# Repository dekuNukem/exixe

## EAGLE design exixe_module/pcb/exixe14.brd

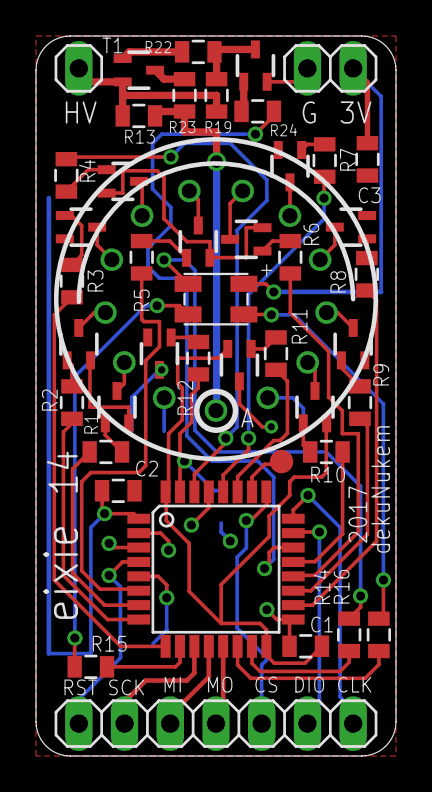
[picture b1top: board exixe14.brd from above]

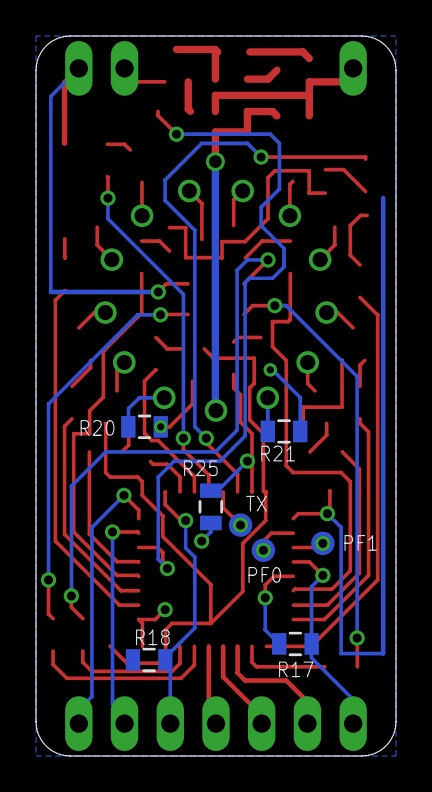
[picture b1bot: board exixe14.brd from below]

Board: 2 copper layers, 20.0 x 40.0 mm, 51 parts (8 on the bottom side), 64 nets.

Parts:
C1: 1uF; 0805
C2, C3: 100nF; 0805
D1: RGB_LED_CA-150141M173100-R&G&B; 3528-COMMON-ANODE
JP1, JP2: 1X07
N1: IN-14
Q1, Q2, Q3, Q4, Q5, Q6, Q7, Q8, Q9, Q10, Q11, Q12, Q13: SOT323
R1, R2, R3, R4, R5, R7, R8, R9, R10, R11, R12, R17, R18, R24: 10K; 0805
R6: 4K7; 0805
R13, R23, R25: 68K; 0805
R14, R16: 330; 0805
R15: 680; 0805
R19, R22: 1M; 0805
R20, R21: 510K; 0805
T1: SOT323
TP1, TP2, TP3, TP4: PTR1TP13R; TP13R
U$2: STM32F042K6; TQFP32-08

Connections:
+3V3: C1.1, C2.1, C3.1, D1.1, JP1.7, R17.2, R18.2, U$2.1, U$2.5, U$2.17
+180V: N1.A, R13.1, R23.1
BAKE: R24.2, U$2.22
GND: C1.2, C2.2, C3.2, JP1.6, Q1.2, Q2.2, Q3.2, Q4.2, Q5.2, Q6.2, Q7.2, Q8.2, Q9.2, Q10.2, Q11.2, Q12.2, Q13.2, R25.1, U$2.16, U$2.32
unnamed: Q1.1, R1.2
unnamed: TP1.TP, U$2.2
unnamed: D1.4, R15.1
unnamed: Q2.1, R2.2
unnamed: Q3.1, R3.2
unnamed: Q4.1, R4.2
unnamed: Q5.1, R5.2
unnamed: Q6.1, R6.2
unnamed: Q7.1, R7.2
unnamed: Q8.1, R8.2
unnamed: Q9.1, R9.2
unnamed: Q10.1, R10.2
unnamed: Q11.1, R11.2
unnamed: Q12.1, R12.2
unnamed: D1.3, R14.1
unnamed: TP2.TP, U$2.3
unnamed: Q12.3, R21.1
unnamed: Q11.3, R20.1
unnamed: JP1.1, R13.2, R19.1, T1.3
unnamed: R22.1, T1.2
unnamed: D1.2, R16.1
unnamed: Q13.3, R19.2, R22.2
unnamed: Q13.1, R24.1
unnamed: R23.2, T1.1
unnamed: TP4.TP, U$2.26
NIXIE_1: N1.1, Q1.3
NIXIE_2: N1.2, Q2.3
NIXIE_3: N1.3, Q3.3
NIXIE_4: N1.4, Q4.3
NIXIE_5: N1.5, Q5.3
NIXIE_6: N1.6, Q6.3
NIXIE_7: N1.7, Q7.3
NIXIE_8: N1.8, Q8.3
NIXIE_9: N1.9, Q9.3
NIXIE_10: N1.0, Q10.3
NIXIE_DOT_LEFT: N1.LHDP, R20.2
NIXIE_DOT_RIGHT: N1.RHDP, R21.2
NRST: JP2.1, R17.1, U$2.4
PWM_BLUE: R16.2, U$2.14
PWM_GREEN: R15.2, U$2.10
PWM_RED: R14.2, U$2.15
SPI_CS: JP2.5, R18.1, U$2.25
SPI_MISO: JP2.3, U$2.12
SPI_MOSI: JP2.4, U$2.13
SPI_SCK: JP2.2, U$2.11
STM_1: R1.1, U$2.7
STM_2: R2.1, U$2.8
STM_3: R3.1, U$2.9
STM_4: R4.1, U$2.30
STM_5: R5.1, U$2.6
STM_6: R6.1, U$2.20
STM_7: R7.1, U$2.28
STM_8: R8.1, U$2.18
STM_9: R9.1, U$2.19
STM_10: R10.1, U$2.21
STM_DOT_LEFT: R11.1, U$2.27
STM_DOT_RIGHT: R12.1, R25.2, U$2.31
SWD_CLK: JP2.7, U$2.24
SWD_DIO: JP2.6, U$2.23
UART_TX: TP3.TP, U$2.29

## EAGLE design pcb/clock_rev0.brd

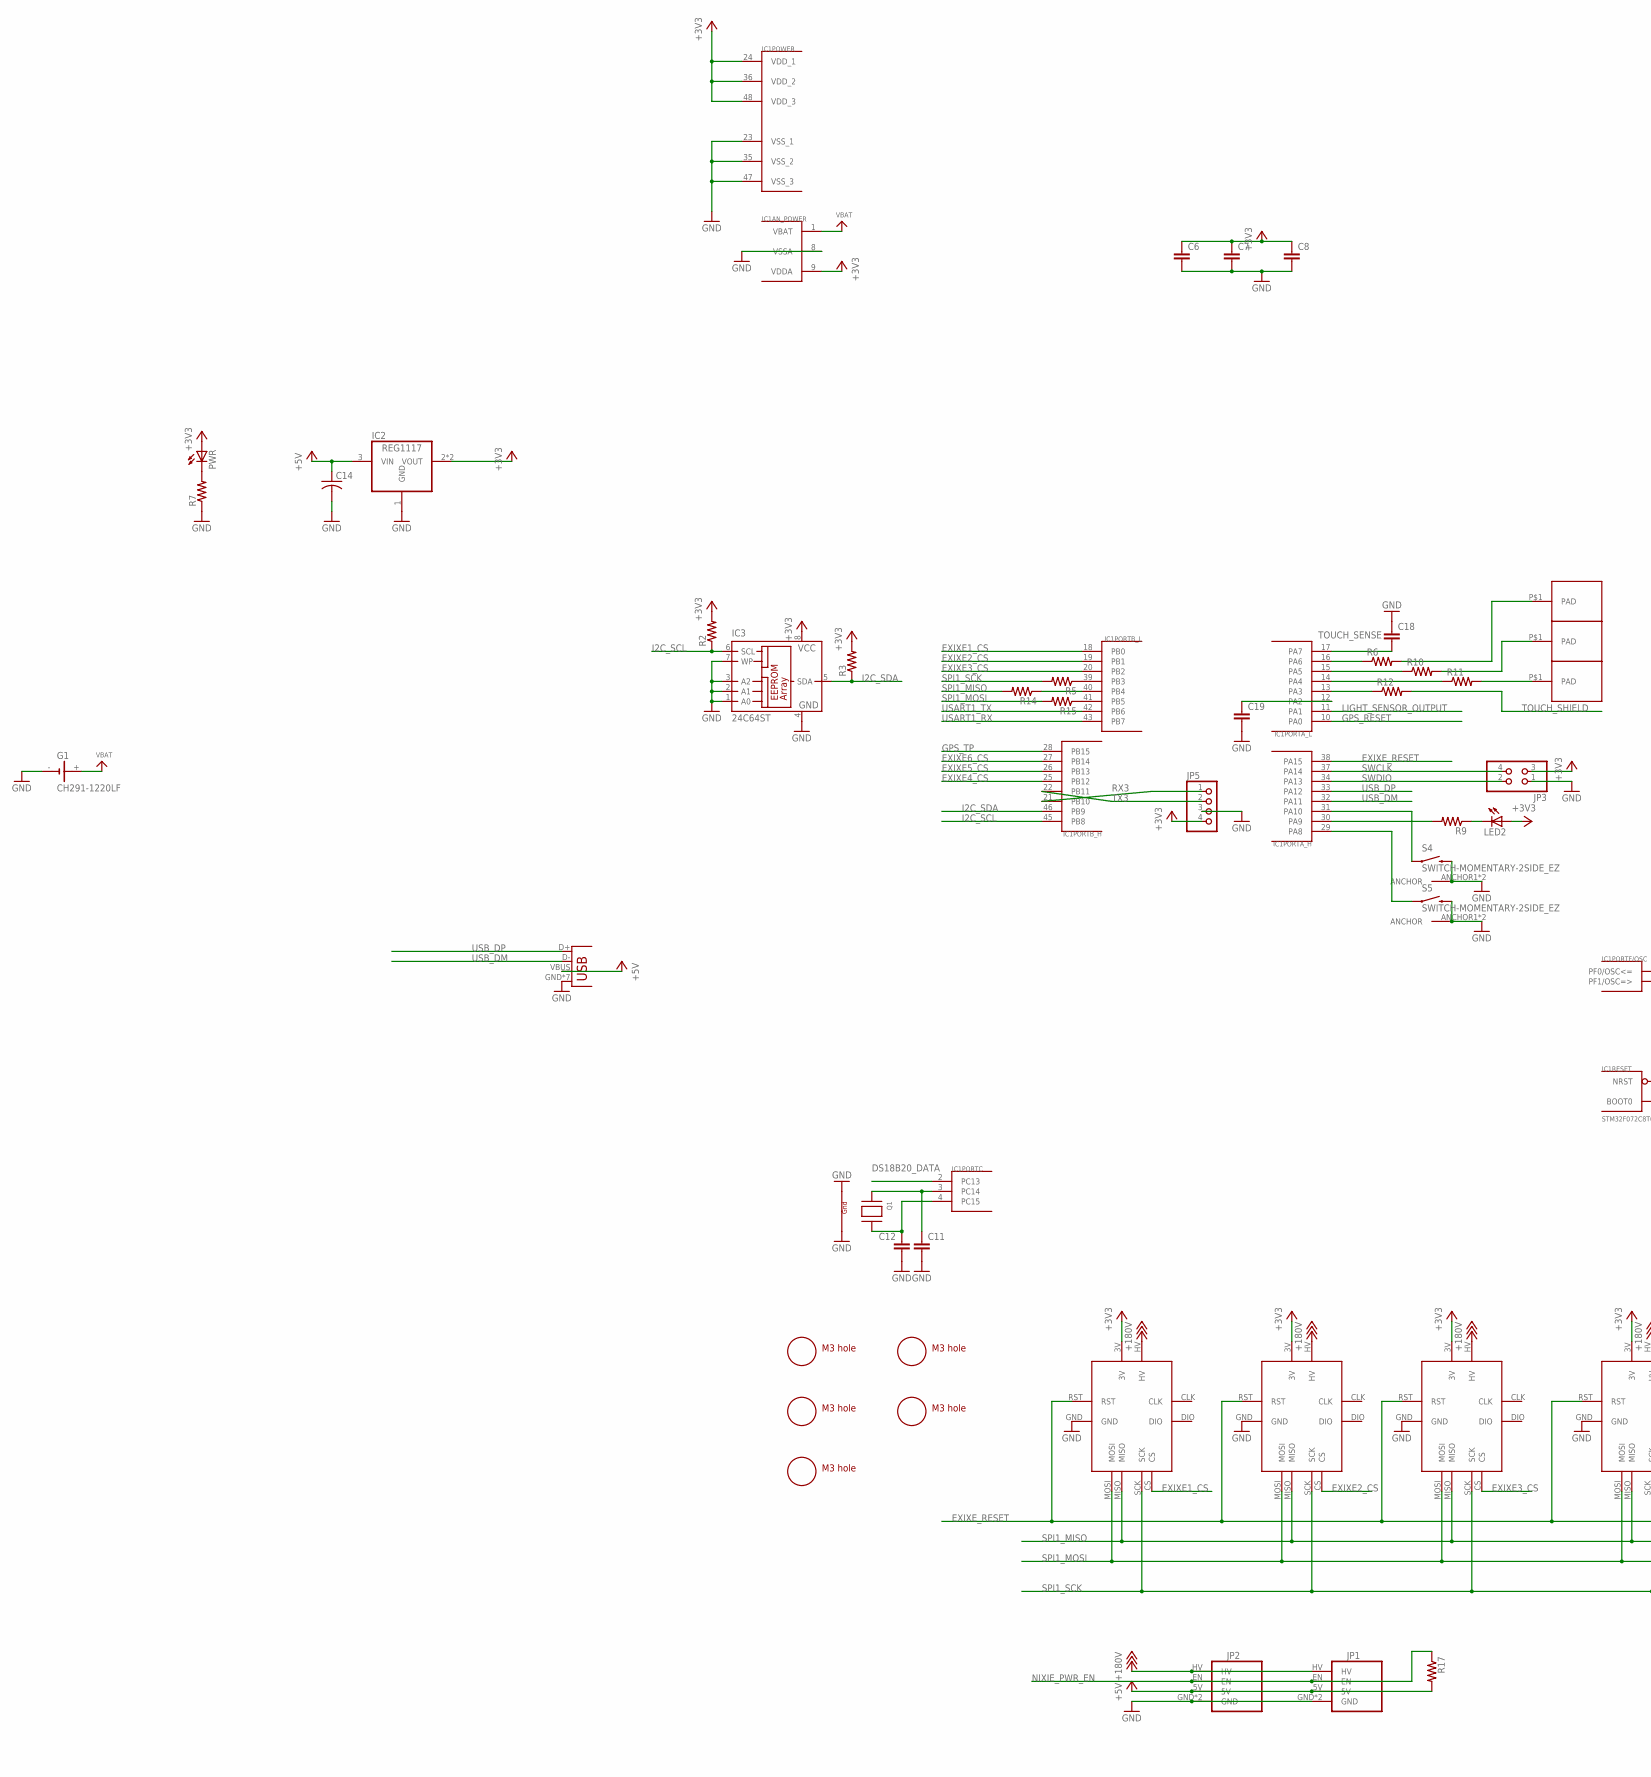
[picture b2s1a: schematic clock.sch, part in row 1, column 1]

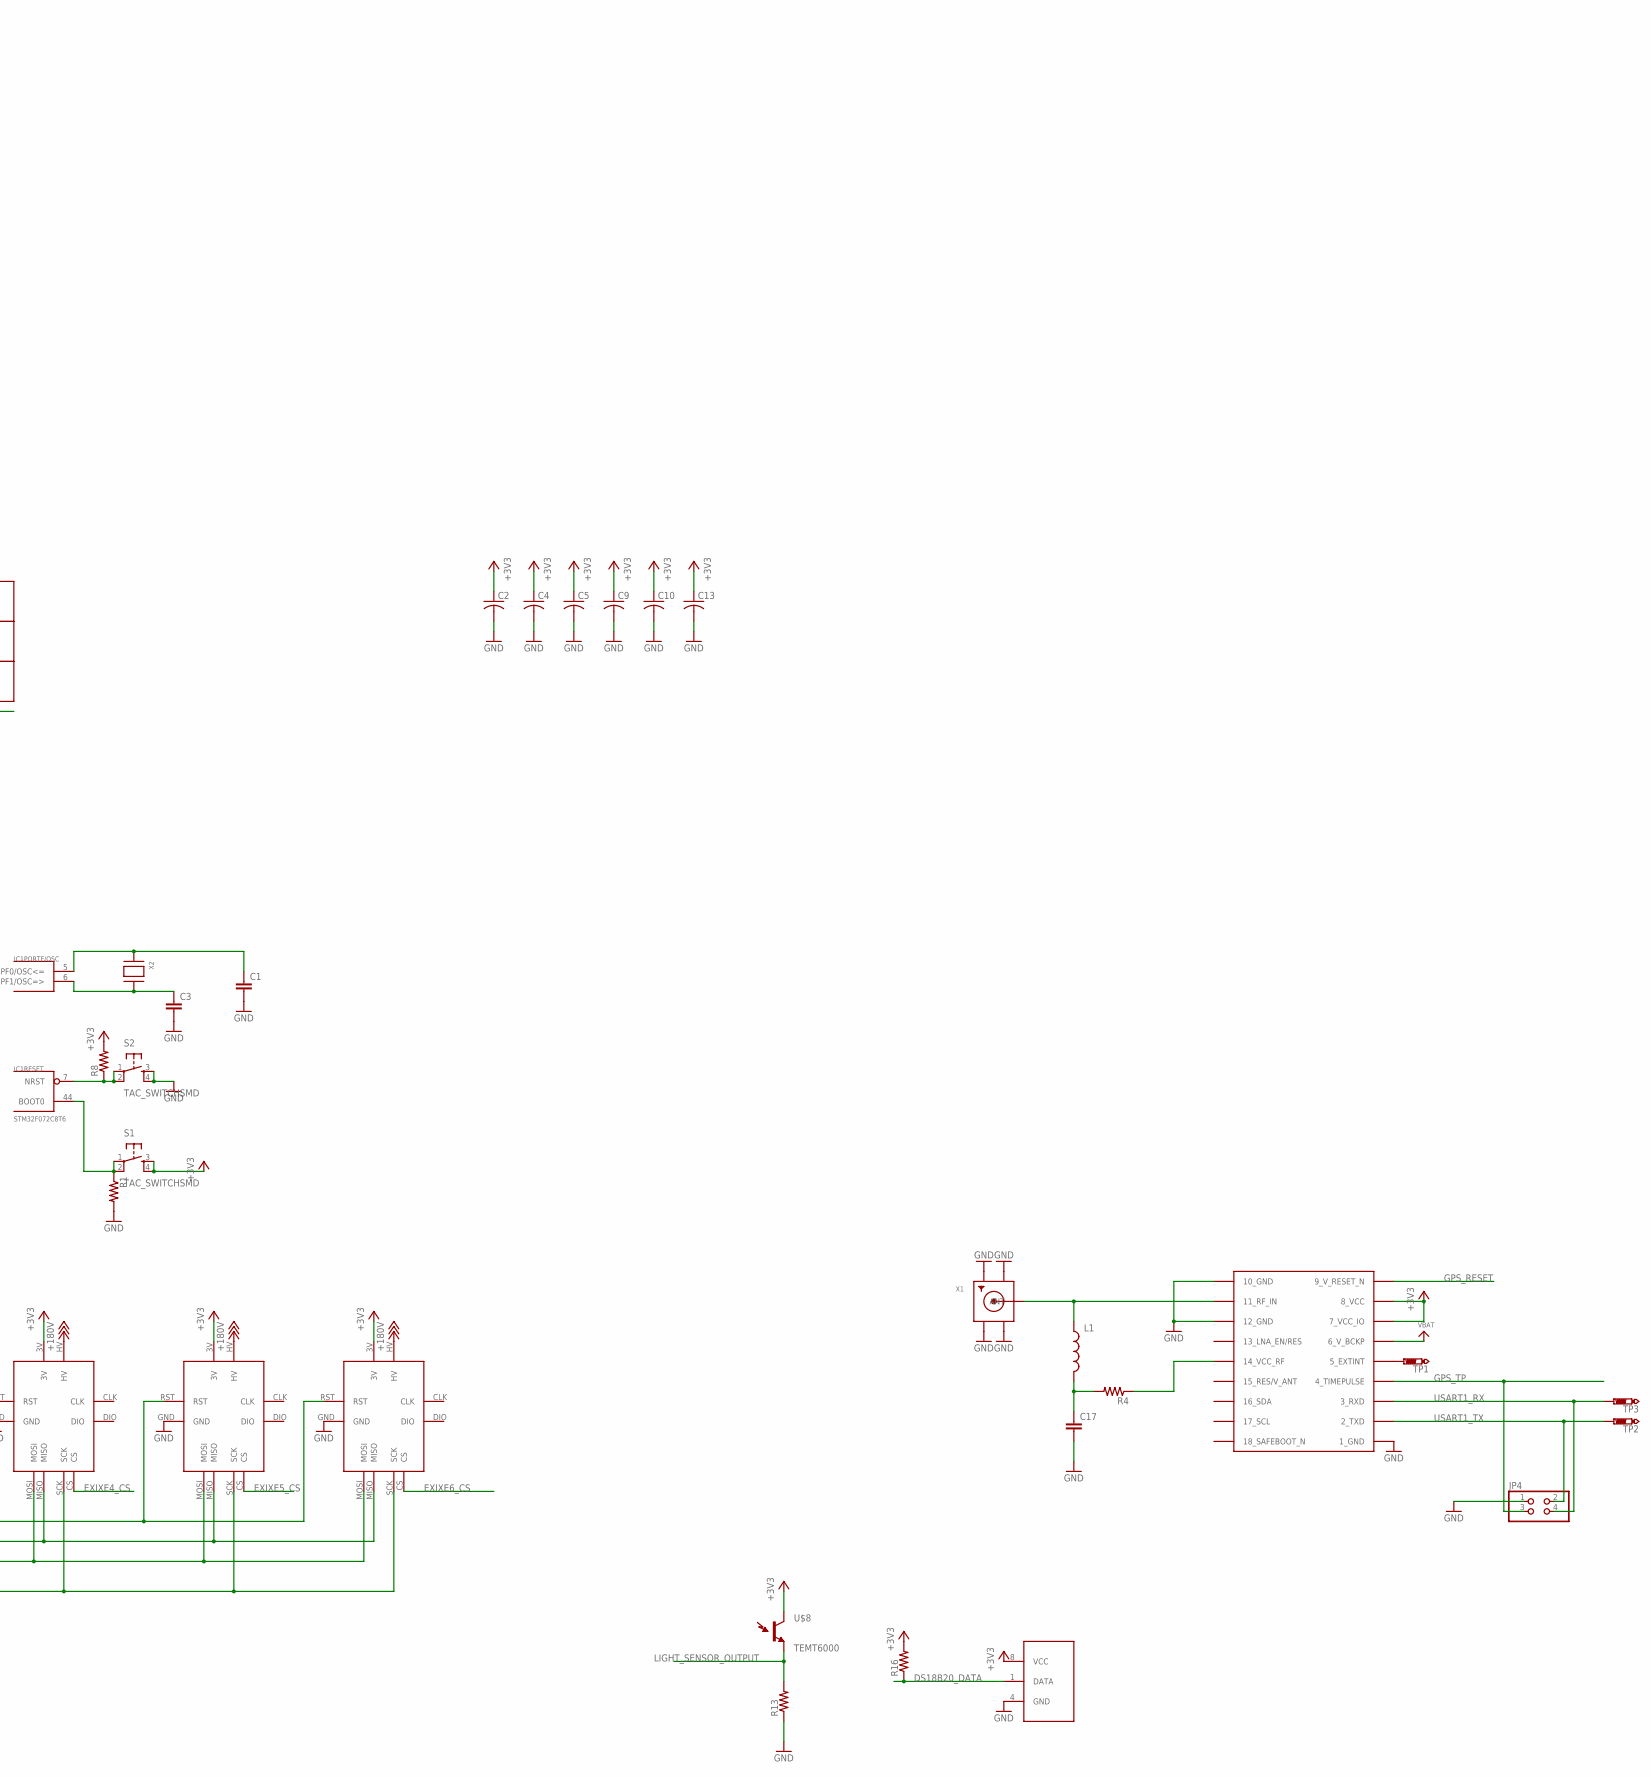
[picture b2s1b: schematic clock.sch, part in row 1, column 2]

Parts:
C1, C3, C6, C7, C8, C11, C12, C17, C18, C19: CAP0805; 0805
C2, C4, C5, C9, C10, C13, C14: C-USC1210; C1210
G1: CH291-1220LF
IC1: STM32F072C8T6; TQFP48
IC2: REG1117; SOT223
IC3: 24C64ST; TSSOP8
JP1: EBAY_MODULEEBAY; EBAY_PKG
JP2: EBAY_MODULETAOBAO; TAOBAO_PKG
JP3, JP4: PINHD-2X2; 2X02
JP5: PINHD-1X4; 1X04
L1: INDUCTOR0805; 0805
LED2: LEDCHIP-LED0805; CHIP-LED0805
PWR: LEDCHIP-LED0805; CHIP-LED0805
Q1: XTAL-4-3225; NX3225
R1, R2, R3, R4, R5, R6, R7, R8, R9, R10, R11, R12, R13, R14, R15, R16, R17: RESISTOR0805-RES; 0805
S1, S2: TAC_SWITCHSMD; TACTILE-SWITCH-SMD
S4, S5: SWITCH-MOMENTARY-2SIDE_EZ; TACTILE-PTH-SIDEEZ
TP1, TP2, TP3: PTR1TP20R; TP20R
U$1, U$2, U$3, U$4, U$5, U$6: EXIXE; EXIXE_PAC
U$7: MAX-M8
U$8: TEMT6000; TEMT6000-SEN
U$9: DS18B20; MSOP8
U$10, U$11, U$12, U$13, U$20: M3_MOUNTING_HOLE; M3_MOUNTING_HOLE_PACK
U$14, U$15, U$16: TOUCHPAD; TOUCHPAD_PAK
X1: SMACONNECTOR; SMA90_DIP
X2: XTAL-3.2X1.5; XTAL3215
X3: USB-MICROB

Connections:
+3V3: C2.1, C4.1, C5.1, C6.1, C7.1, C8.1, C9.1, C10.1, C13.1, IC1.9 (VDDA), IC1.24 (VDD_1), IC1.36 (VDD_2), IC1.48 (VDD_3), IC2.2 (VOUT), IC2.4 (VOUT), IC3.8 (VCC), JP3.3, JP5.4, LED2.A, PWR.A, R2.2, R3.2, R8.2, R16.2, S1.3, S1.4, U$1.3V, U$2.3V, U$3.3V, U$4.3V, U$5.3V, U$6.3V, U$7.7_VCC_IO, U$7.8_VCC, U$8.COLLECTOR (C1), U$9.8 (VCC)
+5V: C14.1, IC2.3 (VIN), JP1.5V, JP2.5V, R17.2, X3.VBUS
+180V: JP1.HV, JP2.HV, U$1.HV, U$2.HV, U$3.HV, U$4.HV, U$5.HV, U$6.HV
DS18B20_DATA: IC1.2 (PC13), R16.1, U$9.1 (DATA)
EXIXE1_CS: IC1.18 (PB0), U$1.CS
EXIXE2_CS: IC1.19 (PB1), U$2.CS
EXIXE3_CS: IC1.20 (PB2), U$3.CS
EXIXE4_CS: IC1.25 (PB12), U$4.CS
EXIXE5_CS: IC1.26 (PB13), U$5.CS
EXIXE6_CS: IC1.27 (PB14), U$6.CS
EXIXE_RESET: IC1.38 (PA15), U$1.RST, U$2.RST, U$3.RST, U$4.RST, U$5.RST, U$6.RST
GND: C1.2, C2.2, C3.2, C4.2, C5.2, C6.2, C7.2, C8.2, C9.2, C10.2, C11.2, C12.2, C13.2, C14.2, C17.2, C18.1, C19.2, G1.-, IC1.8 (VSSA), IC1.23 (VSS_1), IC1.35 (VSS_2), IC1.47 (VSS_3), IC2.1 (GND), IC3.1 (A0), IC3.2 (A1), IC3.3 (A2), IC3.4 (GND), IC3.7 (WP), JP1.GND, JP1.GND2 (GND), JP2.GND, JP2.GND2 (GND), JP3.1, JP4.1, JP5.3, Q1.2 (G2), Q1.4 (G1), R1.2, R7.1, R13.1, S2.3, S2.4, S4.2, S4.ANCHOR1 (ANCHOR), S4.ANCHOR2 (ANCHOR), S5.2, S5.ANCHOR1 (ANCHOR), S5.ANCHOR2 (ANCHOR), U$1.GND, U$2.GND, U$3.GND, U$4.GND, U$5.GND, U$6.GND, U$7.1_GND, U$7.10_GND, U$7.12_GND, U$9.4 (GND), X1.GND1, X1.GND2, X1.GND3, X1.GND4, X3.GND, X3.P1 (GND), X3.P2 (GND), X3.P3 (GND), X3.P4 (GND), X3.P5 (GND), X3.P6 (GND)
GPS_RESET: IC1.10 (PA0), U$7.9_RESET_N (9_V_RESET_N)
GPS_TP: IC1.28 (PB15), JP4.3, U$7.4_TIMEPULSE
I2C_SCL: IC1.45 (PB8), IC3.6 (SCL), R2.1
I2C_SDA: IC1.46 (PB9), IC3.5 (SDA), R3.1
LIGHT_SENSOR_OUTPUT: IC1.11 (PA1), R13.2, U$8.EMITTER (E1)
unnamed: C11.1, IC1.3 (PC14), Q1.1 (X1)
unnamed: C12.1, IC1.4 (PC15), Q1.3 (X2)
unnamed: IC1.7 (NRST), R8.1, S2.1, S2.2
unnamed: L1.1, U$7.11_RF_IN, X1.ANTENNA (ANT)
unnamed: IC1.44 (BOOT0), R1.1, S1.1, S1.2
unnamed: C3.1, IC1.6 (PF1/OSC=>), X2.P$2
unnamed: C1.1, IC1.5 (PF0/OSC<=), X2.P$1
unnamed: IC1.14 (PA4), R11.1
unnamed: R10.2, U$15.P$1
unnamed: R6.2, U$16.P$1
unnamed: IC1.13 (PA3), R12.1
unnamed: C17.1, L1.2, R4.2
unnamed: R4.1, U$7.14_VCC_RF
unnamed: R11.2, U$14.P$1
unnamed: IC1.15 (PA5), R10.1
unnamed: IC1.16 (PA6), R6.1
unnamed: IC1.39 (PB3), R5.1
unnamed: C19.1, IC1.12 (PA2)
unnamed: IC1.41 (PB5), R15.1
unnamed: IC1.40 (PB4), R14.1
unnamed: LED2.C, R9.1
unnamed: IC1.31 (PA10), S4.1
unnamed: IC1.29 (PA8), S5.1
unnamed: IC1.30 (PA9), R9.2
unnamed: TP1.TP, U$7.5_EXTINT
unnamed: PWR.C, R7.2
NIXIE_PWR_EN: JP1.EN, JP2.EN, R17.1
PB10: IC1.21 (PB10), JP5.1
PB11: IC1.22 (PB11), JP5.2
SPI1_MISO: R14.2, U$1.MISO, U$2.MISO, U$3.MISO, U$4.MISO, U$5.MISO, U$6.MISO
SPI1_MOSI: R15.2, U$1.MOSI, U$2.MOSI, U$3.MOSI, U$4.MOSI, U$5.MOSI, U$6.MOSI
SPI1_SCK: R5.2, U$1.SCK, U$2.SCK, U$3.SCK, U$4.SCK, U$5.SCK, U$6.SCK
SWCLK: IC1.37 (PA14), JP3.4
SWDIO: IC1.34 (PA13), JP3.2
TOUCH_SENSE: C18.2, IC1.17 (PA7)
TOUCH_SHIELD: R12.2
USART1_RX: IC1.43 (PB7), JP4.4, TP3.TP, U$7.3_RXD
USART1_TX: IC1.42 (PB6), JP4.2, TP2.TP, U$7.2_TXD
USB_DM: IC1.32 (PA11), X3.D-
USB_DP: IC1.33 (PA12), X3.D+
VBAT: G1.+, IC1.1 (VBAT), U$7.6_V_BCKP

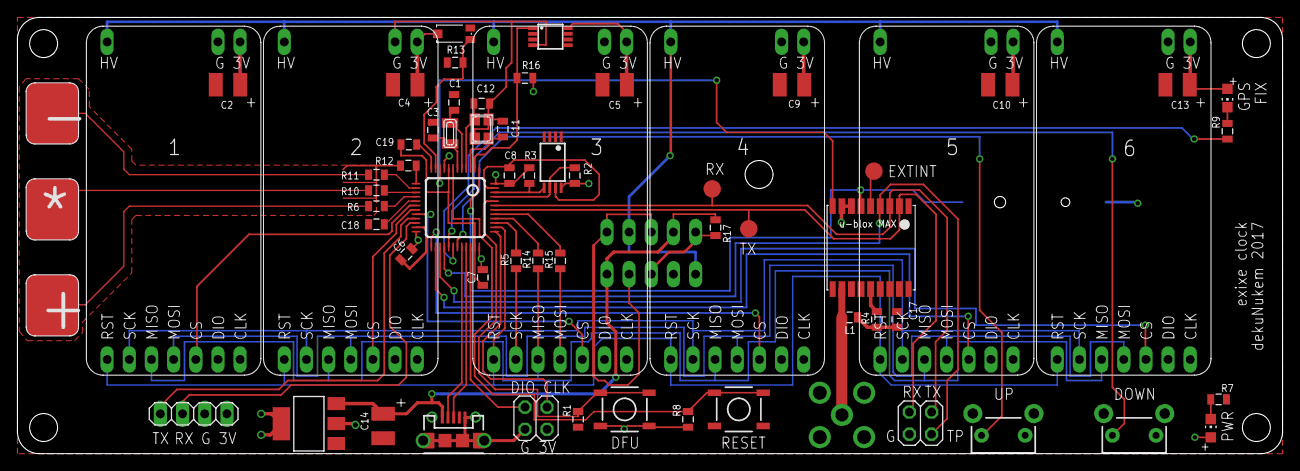
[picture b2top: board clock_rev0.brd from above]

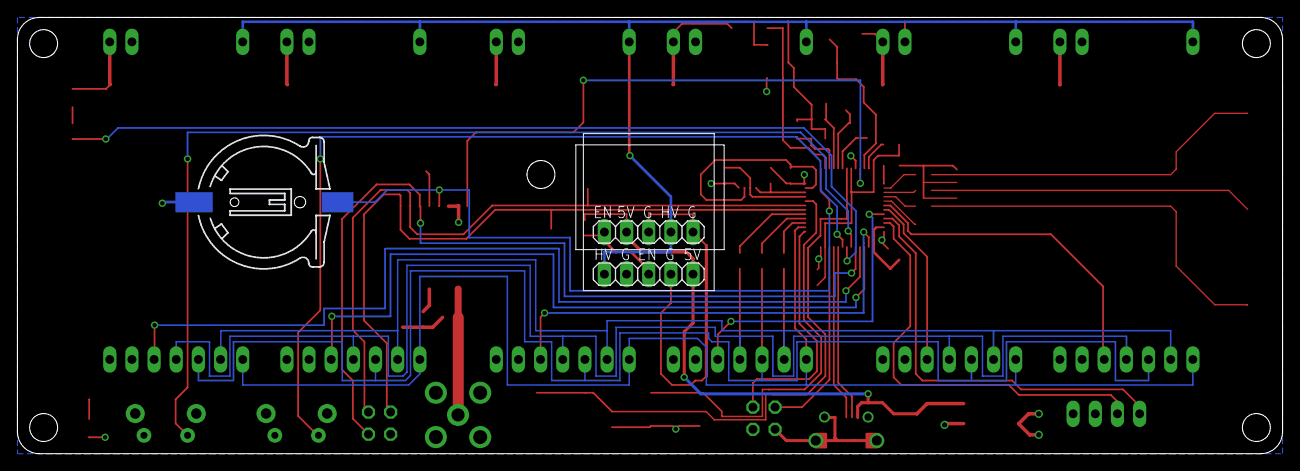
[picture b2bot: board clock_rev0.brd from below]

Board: 2 copper layers, 145.0 x 50.0 mm, 74 parts (3 on the bottom side), 57 nets.

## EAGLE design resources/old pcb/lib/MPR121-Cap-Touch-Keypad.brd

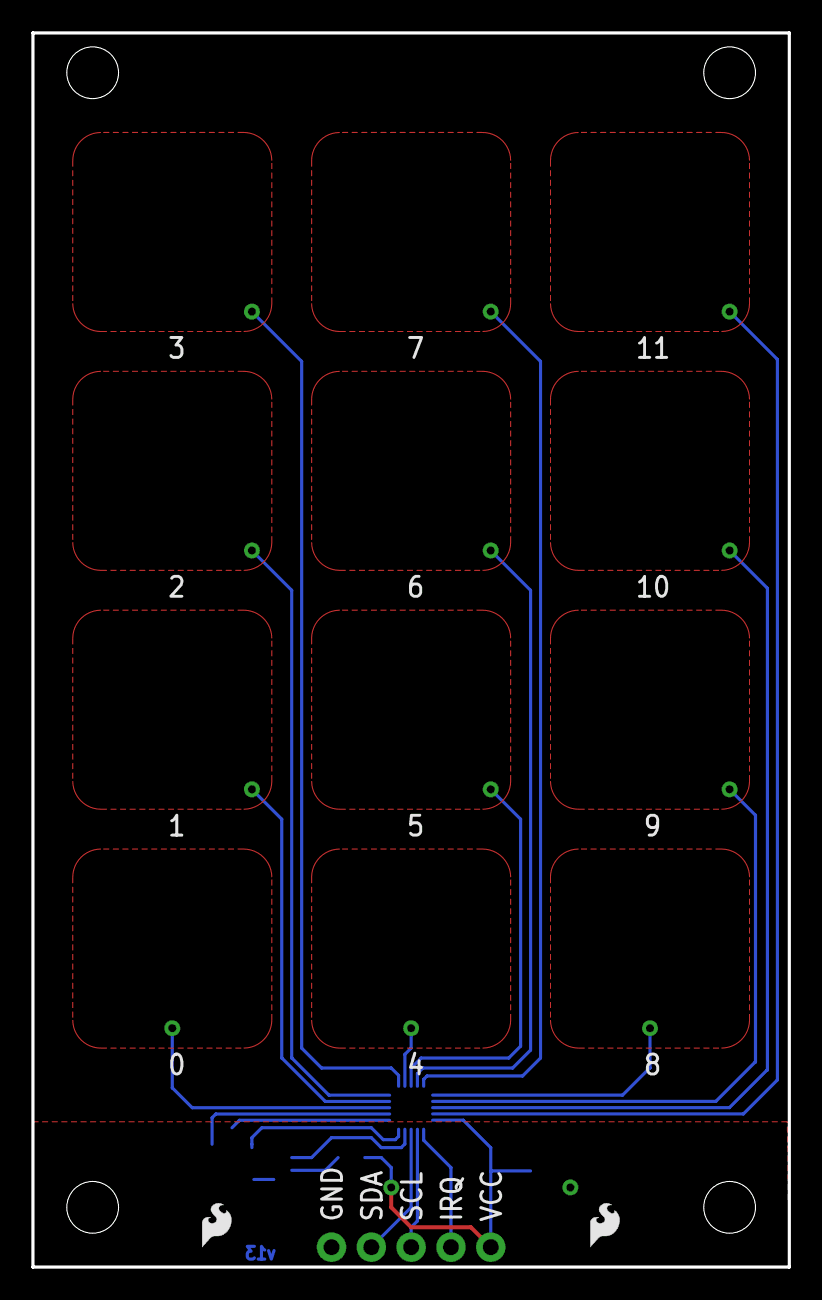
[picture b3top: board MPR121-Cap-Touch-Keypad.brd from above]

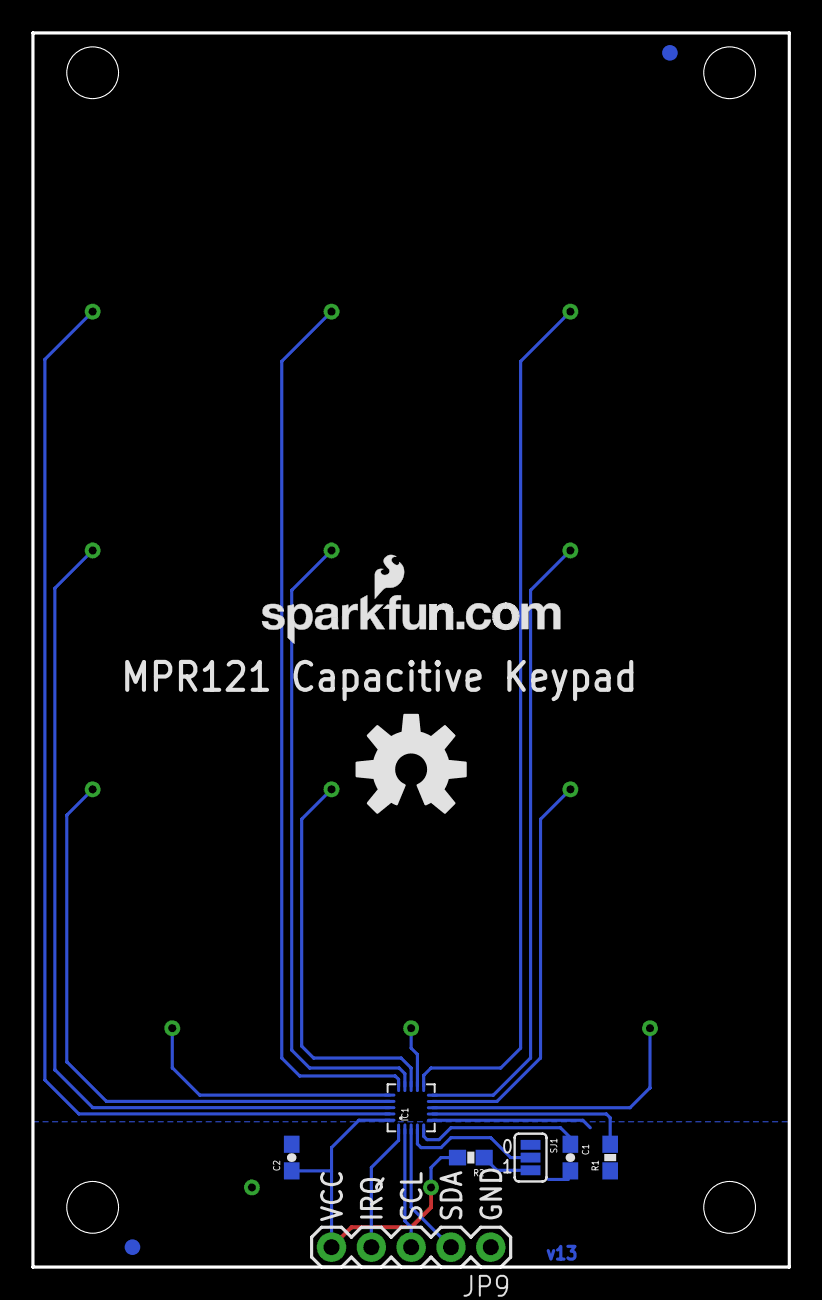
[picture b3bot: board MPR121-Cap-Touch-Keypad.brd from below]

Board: 2 copper layers, 48.3 x 78.7 mm, 19 parts (15 on the bottom side), 9 nets.

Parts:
C1, C2: 0.1uF; 0603-CAP
FRAME1: FRAME-LETTER; CREATIVE_COMMONS
IC1: MPR121; QFN-20-0.4MM-V2
JP1: LOGO-SFENEW; SFE-NEW-WEBLOGO
JP2, JP6: LOGO-SFESK; SFE-LOGO-FLAME
JP3, JP4, JP7, JP8: STAND-OFF
JP5, JP10: FIDUCIAL1X2; FIDUCIAL-1X2
JP9: 1X05
LOGO1: OSHW-LOGOL; OSHW-LOGO-L
R1: 75k; 0603-RES
R2: 10K; 0603-RES
SJ1: SJ_3_PASTE1&2
U$1: REVISION

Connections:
GND: C1.2, C2.2, IC1.6, JP9.1, R1.1, SJ1.1
unnamed: IC1.4, SJ1.2
unnamed: R2.1, SJ1.3
REXT: IC1.7, R1.2
SCL: IC1.2, JP9.3
SDA: IC1.3, JP9.2
VCC: C2.1, IC1.20, JP9.5, R2.2
VREG: C1.1, IC1.5
~IRQ: IC1.1, JP9.4

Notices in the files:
parts and their libraries:
SparkFun-Retired: Licensing:Creative Commons ShareAlike 4.0 International - https://creativecommons.org/licenses/by-sa/4.0
SparkFun-Aesthetics: Licensing: CC v3.0 Share-Alike You are welcome to use this library for commercial purposes.
